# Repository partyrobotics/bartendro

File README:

Programs for the various systems of the Bartendro drink dispensing robot.

Created by Pierre Michael and Robert Kaye
Copyright (c) Party Robotics 2010-2013

All of the source code in this repository is licensed under the GNU Public License 2.0.
The hardware schematic and layouts are licensed using the Creative Commons 
Attribution-ShareAlike 3.0 Unported license.

The source tree is laid out as follows:

hardware -- schematics and layouts for the dispenser and router hardware boards
firmware -- source code (C) for the dispenser and router boards
scripts  -- scripts to make running the bartendro software easier
tsb      -- legacy code from our old skool drink bot prototyp Tequila Sunrise Bot
ui       -- web interface for the bot, written in python.

These various subdirectories may contain more README and COPYING files.

== Downloading updated SD Card images ==

In 2021 the SD card images were updated. They can be downloaded here:

https://github.com/partyrobotics/bartendro/releases/tag/v-2021-05-21

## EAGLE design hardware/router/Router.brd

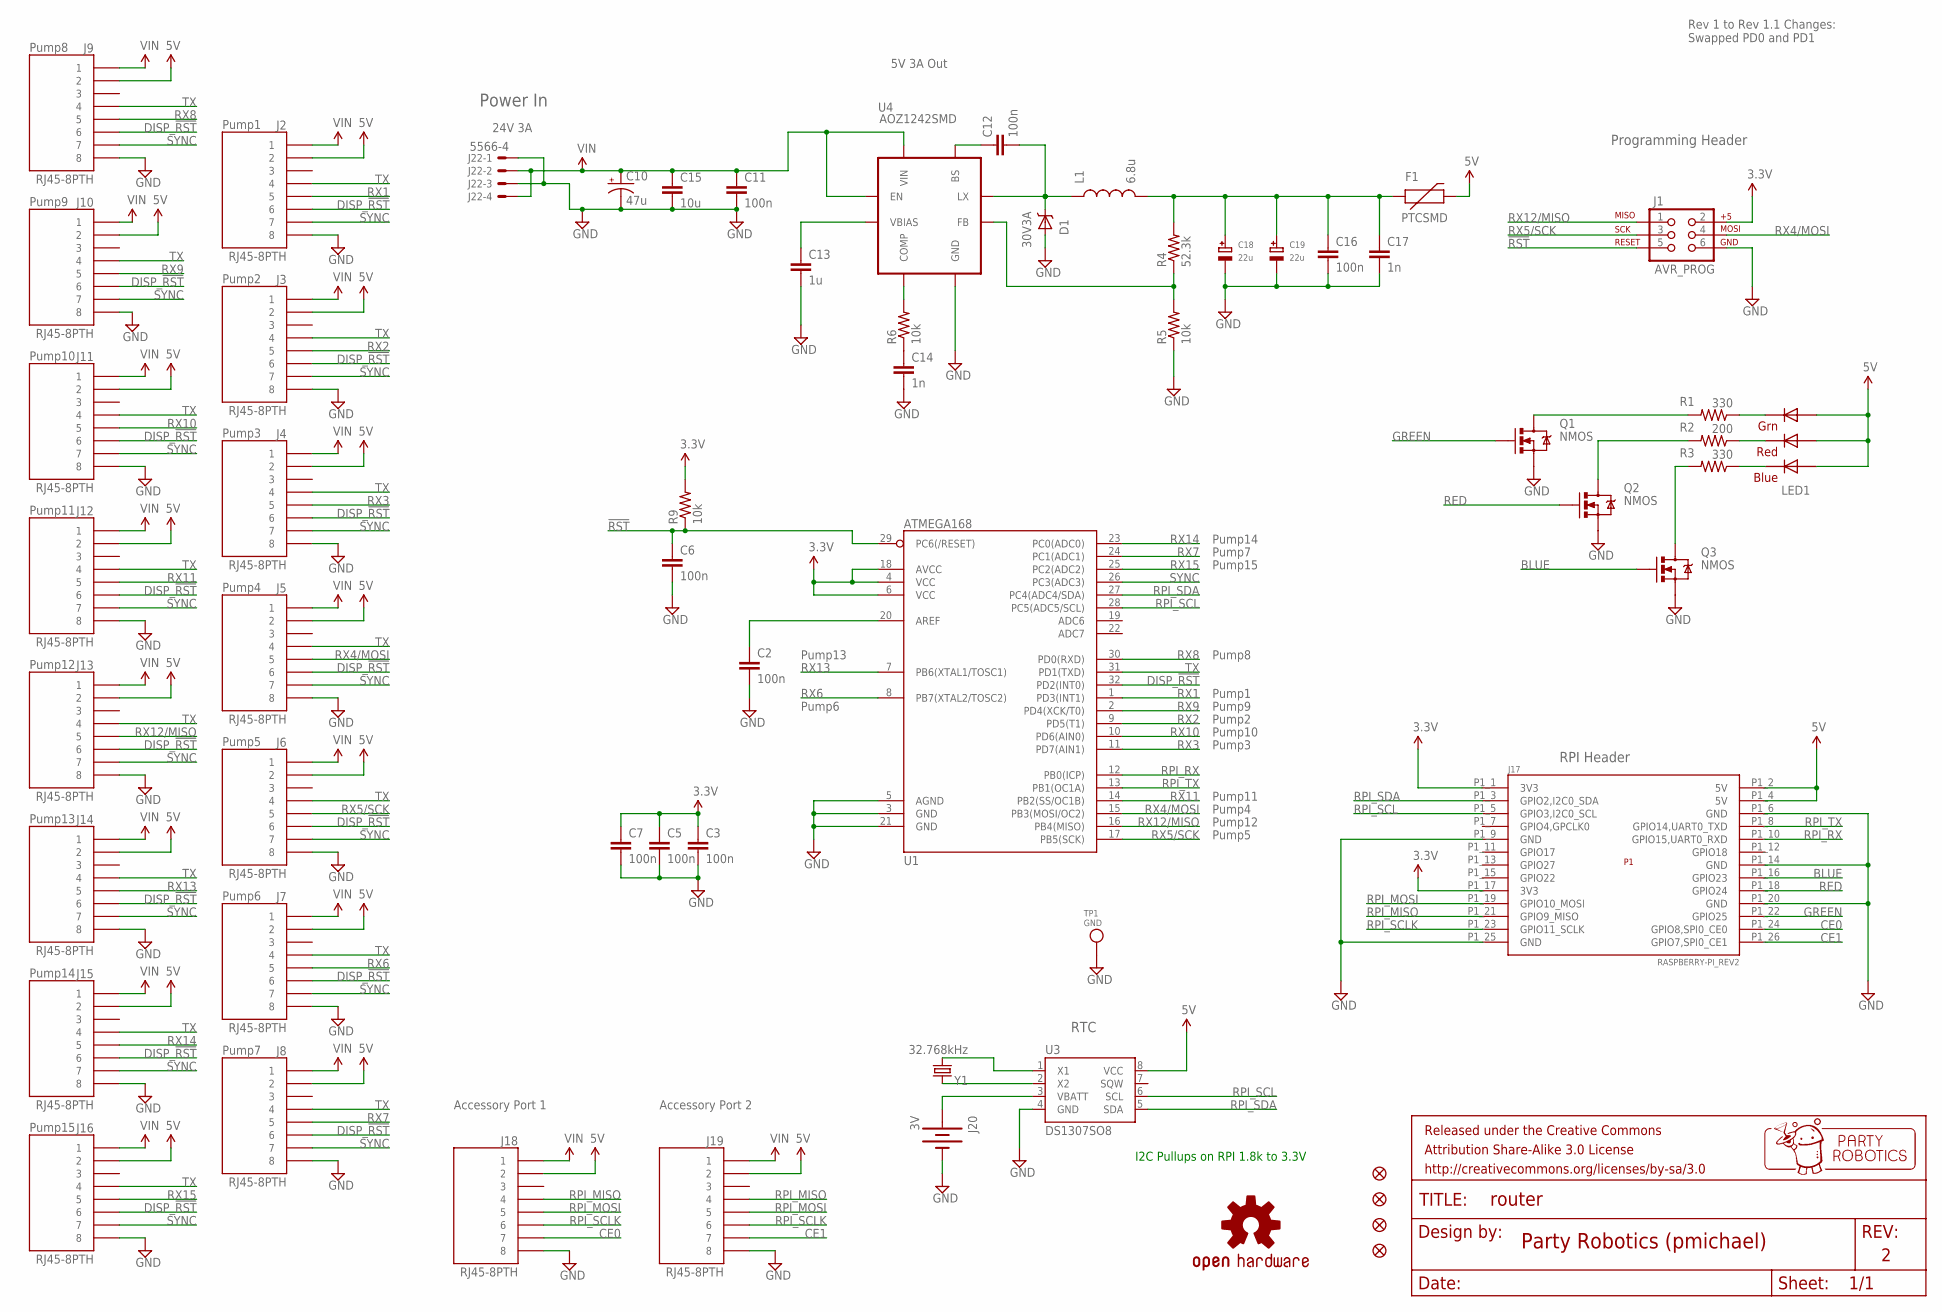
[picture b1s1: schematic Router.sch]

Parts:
C2, C3, C5, C6, C7, C11, C12, C16: 100n; 0603-CAP
C10: 47u; PANASONIC_D
C13: 1u; 0603-CAP
C14, C17: 1n; 0603-CAP
C15: 10u; 1206
C18, C19: 22u; EIA6032-28/C-R
D1: 30V3A; SMA-DIODE
F1: PTCSMD; PTC-1206
FRAME3: FRAME-LETTER; CREATIVE_COMMONS
J1: AVR_PROG; 2X3_LOCK
J2, J3, J4, J5, J6, J7, J8, J10, J11, J12, J13, J14, J15, J16, J18, J19: RJ45-8PTH; RJ45-8; MFG_PN A00-108-220-450
J9: RJ45-8PTH; RJ45-8
J17: RASPBERRY-PI_REV2
J20: 3V; BATTCON_12MM_PTH
J22: 5566-4
JP1, JP2, JP3, JP4: FIDUCIAL1.5X3; FIDUCIAL-1.5X3
L1: 6.8u; IND_8X8X4
LED1: RGBLED5050
Q1, Q2, Q3: NMOS; SOT23-3
R1, R3: 330; 0603-RES
R2: 200; 0603-RES
R4: 52.3k; 0603-RES
R5, R6, R9: 10k; 0603-RES
TP1: GND; TESTPOINT_SMT
U1: ATMEGA168; TQFP32-08
U3: DS1307SO8; SO08
U4: AOZ1242SMD; SO08
U$46: OSHW-LOGOM; OSHW-LOGO-M
Y1: 32.768kHz; TC26HEZ

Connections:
3.3V: C3.1, C5.1, C7.1, J1.2, J17.P1_1 (3V3), J17.P1_17 (3V3), R9.2, U1.4 (VCC), U1.6 (VCC), U1.18 (AVCC)
5V: F1.2, J2.2, J3.2, J4.2, J5.2, J6.2, J7.2, J8.2, J9.2, J10.2, J11.2, J12.2, J13.2, J14.2, J15.2, J16.2, J17.P1_2 (5V), J17.P1_4 (5V), J18.2, J19.2, LED1.1 (BLUE_A), LED1.2 (RED_A), LED1.3 (GREEN_A), U3.8 (VCC)
!RST: C6.1, J1.5, R9.1, U1.29 (PC6(/RESET))
BAT1+: J20.VCC@1 (+), U3.3 (VBATT)
BLUE: J17.P1_16 (GPIO23), Q3.1 (G)
CE0: J17.P1_24 (GPIO8,SPI0_CE0), J18.7
CE1: J17.P1_26 (GPIO7,SPI0_CE1), J19.7
DISP_!RST: J2.6, J3.6, J4.6, J5.6, J6.6, J7.6, J8.6, J9.6, J10.6, J11.6, J12.6, J13.6, J14.6, J15.6, J16.6, U1.32 (PD2(INT0))
GND: C2.2, C3.2, C5.2, C6.2, C7.2, C10.-, C11.2, C13.2, C14.2, C15.2, C16.2, C17.2, C18.-, C19.-, D1.A, J1.6, J2.8, J3.8, J4.8, J5.8, J6.8, J7.8, J8.8, J9.8, J10.8, J11.8, J12.8, J13.8, J14.8, J15.8, J16.8, J17.P1_6 (GND), J17.P1_9 (GND), J17.P1_14 (GND), J17.P1_20 (GND), J17.P1_25 (GND), J18.8, J19.8, J20.GND (-), J22.1, J22.3, Q1.2 (S), Q2.2 (S), Q3.2 (S), R5.1, TP1.P$1, U1.3 (GND), U1.5 (AGND), U1.21 (GND), U3.4 (GND), U4.3 (GND)
GREEN: J17.P1_22 (GPIO25), Q1.1 (G)
unnamed: U3.2 (X2), Y1.1
unnamed: R4.1, R5.2, U4.4 (FB)
unnamed: R6.2, U4.5 (COMP)
unnamed: C2.1, U1.20 (AREF)
unnamed: C16.1, C17.1, C18.+, C19.+, F1.1, L1.P$2 (2), R4.2
unnamed: U3.1 (X1), Y1.2
unnamed: C12.1, U4.2 (BS)
unnamed: C13.1, U4.8 (VBIAS)
unnamed: LED1.4 (GREEN_C), R1.1
unnamed: Q1.3 (D), R1.2
unnamed: Q2.3 (D), R2.2
unnamed: LED1.5 (RED_C), R2.1
unnamed: LED1.6 (BLUE_C), R3.1
unnamed: Q3.3 (D), R3.2
unnamed: C14.1, R6.1
unnamed: C12.2, D1.C, L1.P$1 (1), U4.1 (LX)
RED: J17.P1_18 (GPIO24), Q2.1 (G)
RPI_MISO: J17.P1_21 (GPIO9_MISO), J18.4, J19.4
RPI_MOSI: J17.P1_19 (GPIO10_MOSI), J18.5, J19.5
RPI_RX: J17.P1_10 (GPIO15,UART0_RXD), U1.12 (PB0(ICP))
RPI_SCL: J17.P1_5 (GPIO3,I2C0_SCL), U1.28 (PC5(ADC5/SCL)), U3.6 (SCL)
RPI_SCLK: J17.P1_23 (GPIO11_SCLK), J18.6, J19.6
RPI_SDA: J17.P1_3 (GPIO2,I2C0_SDA), U1.27 (PC4(ADC4/SDA)), U3.5 (SDA)
RPI_TX: J17.P1_8 (GPIO14,UART0_TXD), U1.13 (PB1(OC1A))
RX1: J2.5, U1.1 (PD3(INT1))
RX2: J3.5, U1.9 (PD5(T1))
RX3: J4.5, U1.11 (PD7(AIN1))
RX4/MOSI: J1.4, J5.5, U1.15 (PB3(MOSI/OC2))
RX5/SCK: J1.3, J6.5, U1.17 (PB5(SCK))
RX6: J7.5, U1.8 (PB7(XTAL2/TOSC2))
RX7: J8.5, U1.24 (PC1(ADC1))
RX8: J9.5, U1.30 (PD0(RXD))
RX9: J10.5, U1.2 (PD4(XCK/T0))
RX10: J11.5, U1.10 (PD6(AIN0))
RX11: J12.5, U1.14 (PB2(SS/OC1B))
RX12/MISO: J1.1, J13.5, U1.16 (PB4(MISO))
RX13: J14.5, U1.7 (PB6(XTAL1/TOSC1))
RX14: J15.5, U1.23 (PC0(ADC0))
RX15: J16.5, U1.25 (PC2(ADC2))
SYNC: J2.7, J3.7, J4.7, J5.7, J6.7, J7.7, J8.7, J9.7, J10.7, J11.7, J12.7, J13.7, J14.7, J15.7, J16.7, U1.26 (PC3(ADC3))
TX: J2.4, J3.4, J4.4, J5.4, J6.4, J7.4, J8.4, J9.4, J10.4, J11.4, J12.4, J13.4, J14.4, J15.4, J16.4, U1.31 (PD1(TXD))
VIN: C10.+, C11.1, C15.1, J2.1, J3.1, J4.1, J5.1, J6.1, J7.1, J8.1, J9.1, J10.1, J11.1, J12.1, J13.1, J14.1, J15.1, J16.1, J18.1, J19.1, J22.2, J22.4, U4.6 (EN), U4.7 (VIN)

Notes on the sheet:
Programming Header
RTC
Accessory Port 1
I2C Pullups on RPI 1.8k to 3.3V
Accessory Port 2
Pump1
Pump2
Pump9
Pump8
Pump10
Pump11
Pump3
Pump4
Pump12
Pump5
Pump13
Pump6
Pump14
Pump7
Pump15
Rev 1 to Rev 1.1 Changes: Swapped PD0 and PD1
Party Robotics (pmichael)
5V 3A Out
Power In
24V 3A
RPI Header

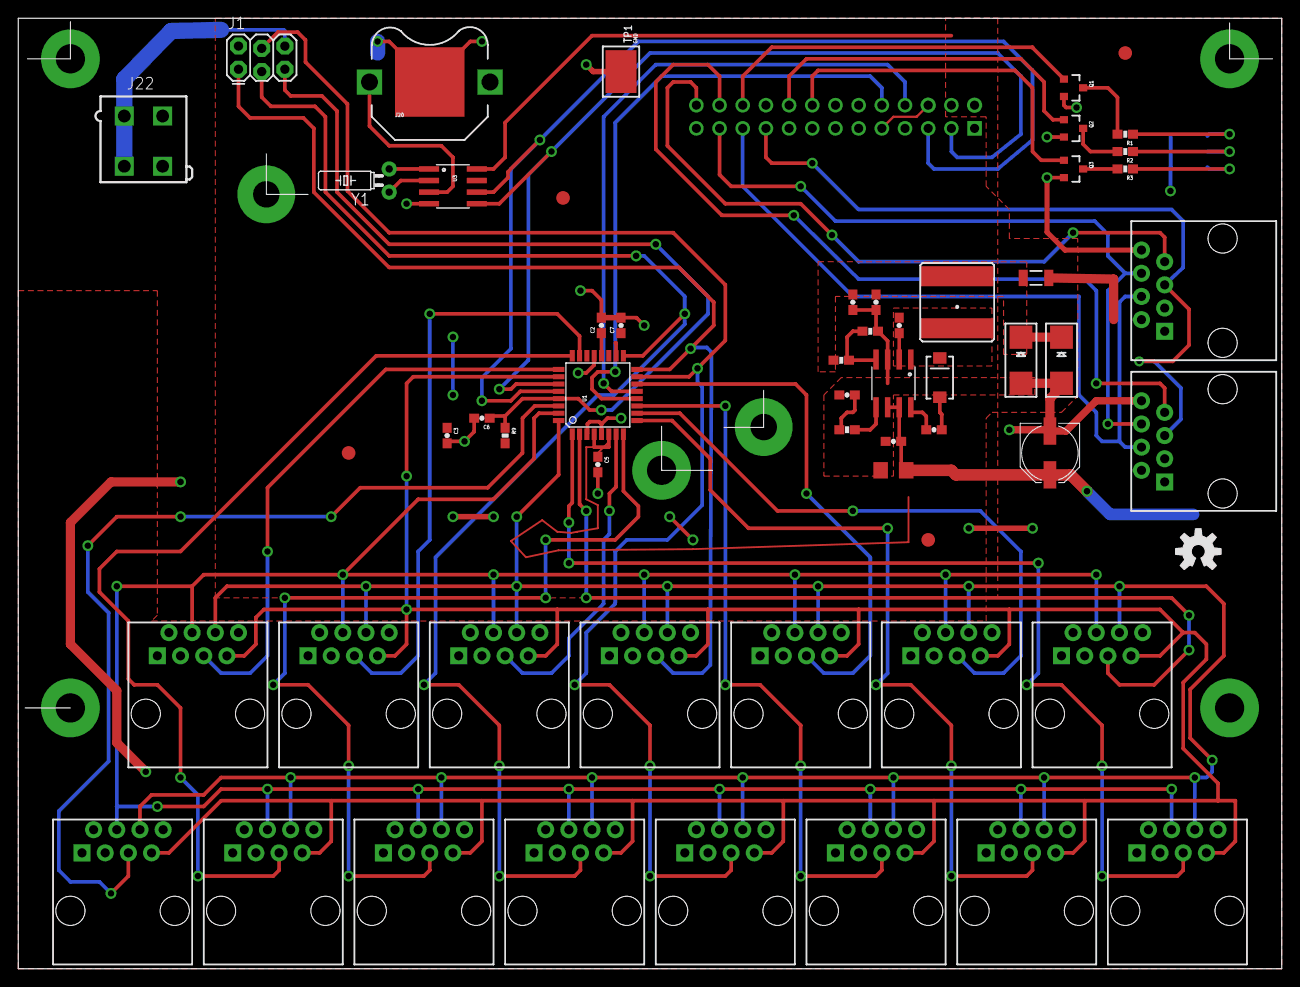
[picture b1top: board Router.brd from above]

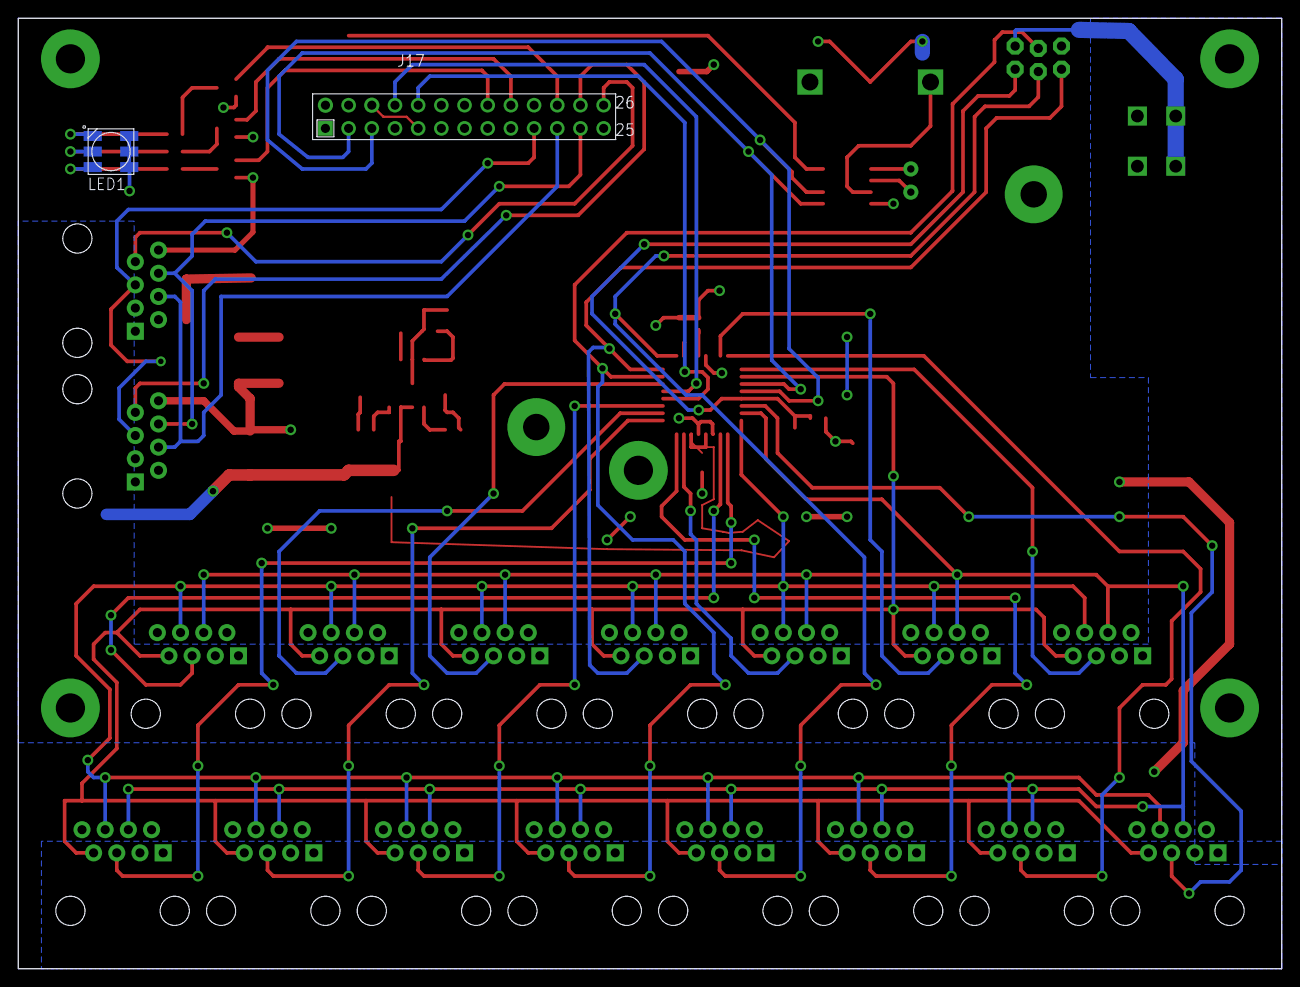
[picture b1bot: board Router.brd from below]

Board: 2 copper layers, 138.4 x 104.1 mm, 61 parts (2 on the bottom side), 52 nets.

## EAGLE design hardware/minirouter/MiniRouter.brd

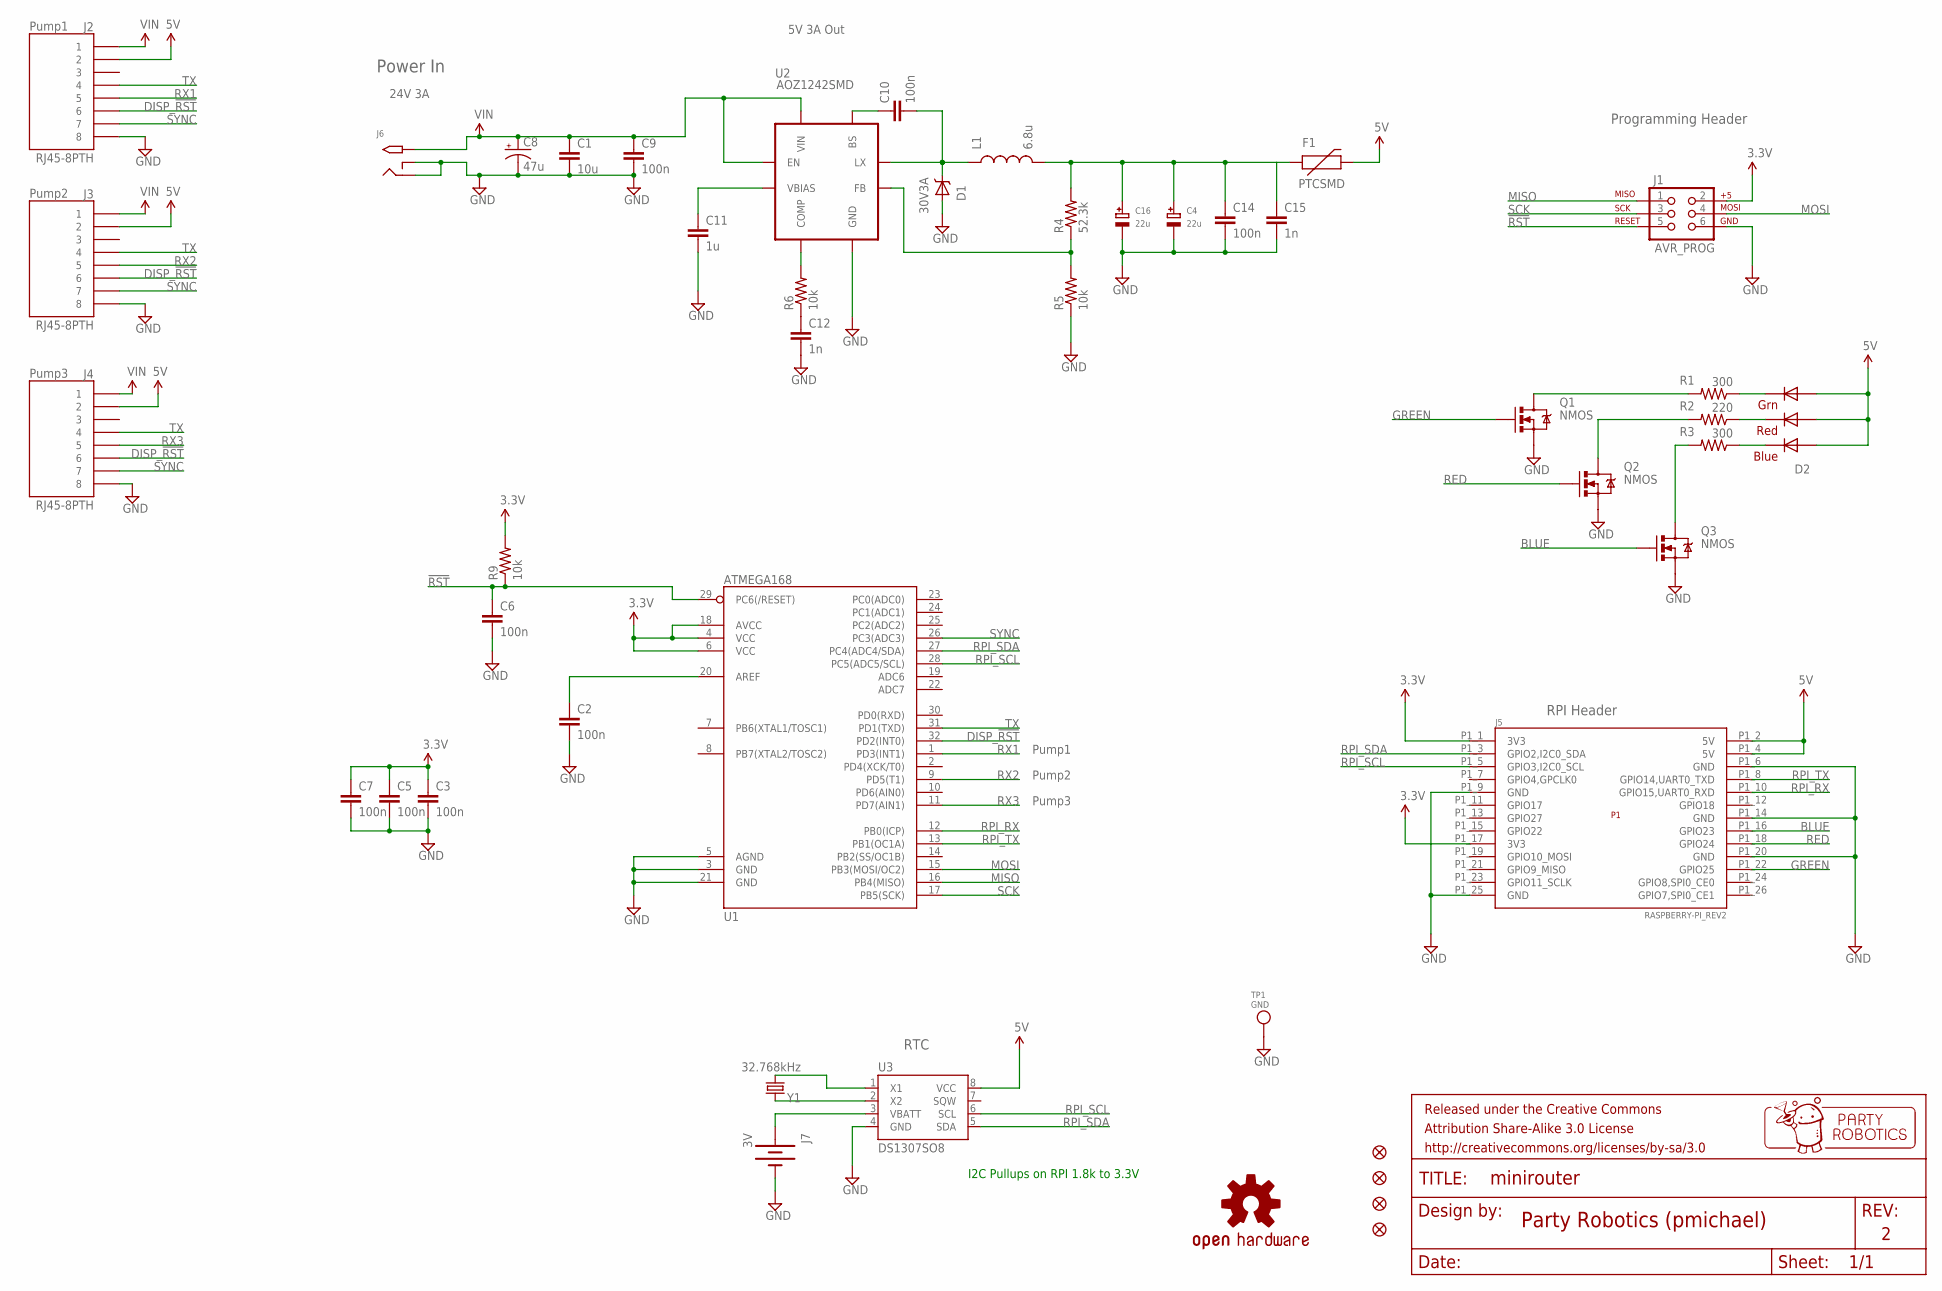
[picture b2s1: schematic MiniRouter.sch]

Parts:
C1: 10u; 1206
C2, C3, C5, C6, C7, C9, C10, C14: 100n; 0603-CAP
C4, C16: 22u; EIA6032-28/C-R
C8: 47u; PANASONIC_D
C11: 1u; 0603-CAP
C12, C15: 1n; 0603-CAP
D1: 30V3A; SMA-DIODE
D2: RGBLED5050
F1: PTCSMD; PTC-1206
FRAME3: FRAME-LETTER; CREATIVE_COMMONS
J1: AVR_PROG; 2X3_LOCK
J2, J3, J4: RJ45-8PTH; RJ45-8
J5: RASPBERRY-PI_REV2
J6: 2.1MMJACKTHM; PJ-102A
J7: 3V; BATTCON_12MM_PTH
JP1, JP2, JP3, JP4: FIDUCIAL1.5X3; FIDUCIAL-1.5X3
L1: 6.8u; IND_8X8X4
Q1, Q2, Q3: NMOS; SOT23-3
R1, R3: 300; 0603-RES
R2: 220; 0603-RES
R4: 52.3k; 0603-RES
R5, R6, R9: 10k; 0603-RES
TP1: GND; TESTPOINT_SMT
U1: ATMEGA168; TQFP32-08
U2: AOZ1242SMD; SO08
U3: DS1307SO8; SO08
U$46: OSHW-LOGOM; OSHW-LOGO-M
Y1: 32.768kHz; TC26HEZ

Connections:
3.3V: C3.1, C5.1, C7.1, J1.2, J5.P1_1 (3V3), J5.P1_17 (3V3), R9.2, U1.4 (VCC), U1.6 (VCC), U1.18 (AVCC)
5V: D2.1 (BLUE_A), D2.2 (RED_A), D2.3 (GREEN_A), F1.2, J2.2, J3.2, J4.2, J5.P1_2 (5V), J5.P1_4 (5V), U3.8 (VCC)
!RST: C6.1, J1.5, R9.1, U1.29 (PC6(/RESET))
BAT1+: J7.VCC@1 (+), U3.3 (VBATT)
BLUE: J5.P1_16 (GPIO23), Q3.1 (G)
DISP_!RST: J2.6, J3.6, J4.6, U1.32 (PD2(INT0))
GND: C1.2, C2.2, C3.2, C4.-, C5.2, C6.2, C7.2, C8.-, C9.2, C11.2, C12.2, C14.2, C15.2, C16.-, D1.A, J1.6, J2.8, J3.8, J4.8, J5.P1_6 (GND), J5.P1_9 (GND), J5.P1_14 (GND), J5.P1_20 (GND), J5.P1_25 (GND), J6.RING, J6.RING_SW, J7.GND (-), Q1.2 (S), Q2.2 (S), Q3.2 (S), R5.1, TP1.P$1, U1.3 (GND), U1.5 (AGND), U1.21 (GND), U2.3 (GND), U3.4 (GND)
GREEN: J5.P1_22 (GPIO25), Q1.1 (G)
MISO: J1.1, U1.16 (PB4(MISO))
MOSI: J1.4, U1.15 (PB3(MOSI/OC2))
unnamed: U3.2 (X2), Y1.1
unnamed: R4.1, R5.2, U2.4 (FB)
unnamed: R6.2, U2.5 (COMP)
unnamed: C2.1, U1.20 (AREF)
unnamed: C4.+, C14.1, C15.1, C16.+, F1.1, L1.P$2 (2), R4.2
unnamed: U3.1 (X1), Y1.2
unnamed: C10.1, U2.2 (BS)
unnamed: C11.1, U2.8 (VBIAS)
unnamed: D2.4 (GREEN_C), R1.1
unnamed: Q1.3 (D), R1.2
unnamed: Q2.3 (D), R2.2
unnamed: D2.5 (RED_C), R2.1
unnamed: D2.6 (BLUE_C), R3.1
unnamed: Q3.3 (D), R3.2
unnamed: C12.1, R6.1
unnamed: C10.2, D1.C, L1.P$1 (1), U2.1 (LX)
RED: J5.P1_18 (GPIO24), Q2.1 (G)
RPI_RX: J5.P1_10 (GPIO15,UART0_RXD), U1.12 (PB0(ICP))
RPI_SCL: J5.P1_5 (GPIO3,I2C0_SCL), U1.28 (PC5(ADC5/SCL)), U3.6 (SCL)
RPI_SDA: J5.P1_3 (GPIO2,I2C0_SDA), U1.27 (PC4(ADC4/SDA)), U3.5 (SDA)
RPI_TX: J5.P1_8 (GPIO14,UART0_TXD), U1.13 (PB1(OC1A))
RX1: J2.5, U1.1 (PD3(INT1))
RX2: J3.5, U1.9 (PD5(T1))
RX3: J4.5, U1.11 (PD7(AIN1))
SCK: J1.3, U1.17 (PB5(SCK))
SYNC: J2.7, J3.7, J4.7, U1.26 (PC3(ADC3))
TX: J2.4, J3.4, J4.4, U1.31 (PD1(TXD))
VIN: C1.1, C8.+, C9.1, J2.1, J3.1, J4.1, J6.TIP, U2.6 (EN), U2.7 (VIN)

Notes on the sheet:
Programming Header
RPI Header
RTC
5V 3A Out
Power In
I2C Pullups on RPI 1.8k to 3.3V
Pump2
Pump3
Pump1
Party Robotics (pmichael)
24V 3A

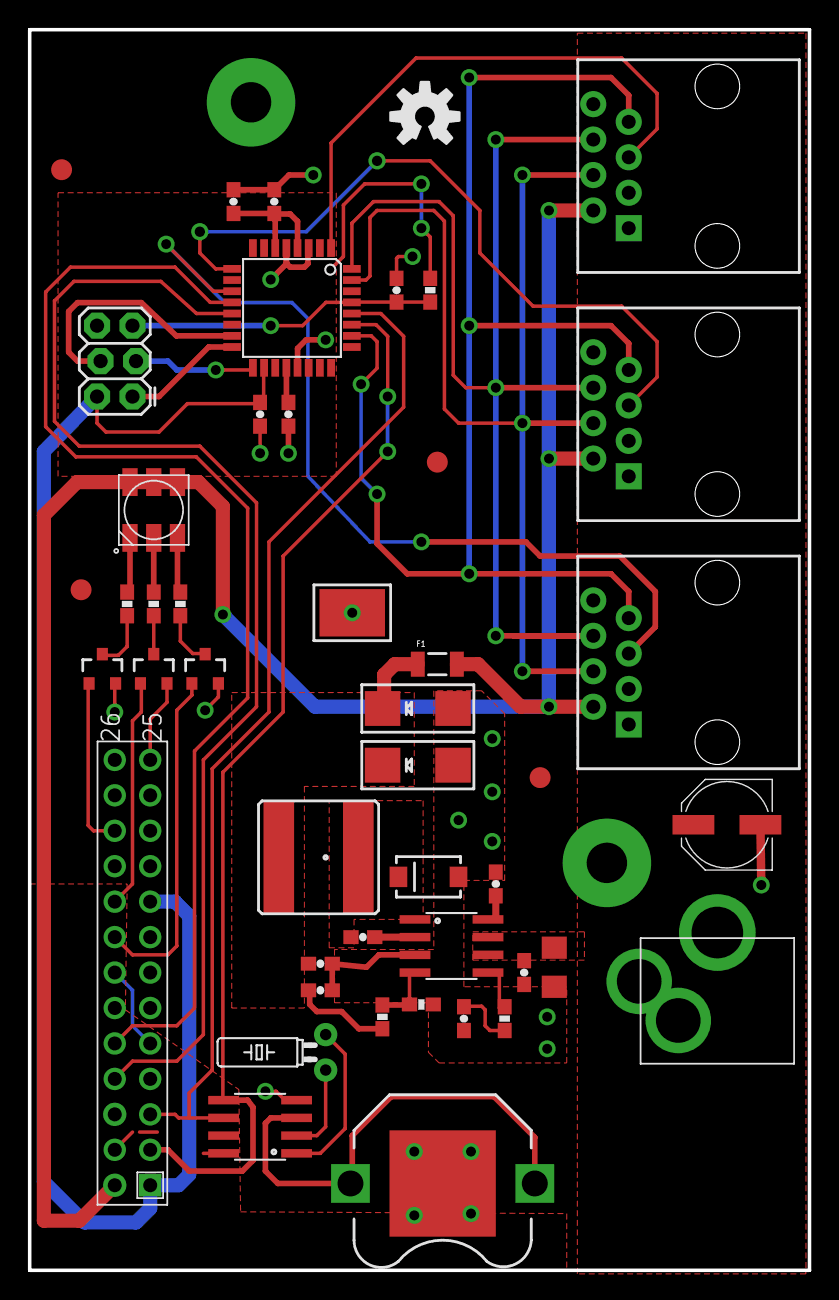
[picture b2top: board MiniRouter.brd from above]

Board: 2 copper layers, 55.9 x 88.9 mm, 47 parts (0 on the bottom side), 38 nets.

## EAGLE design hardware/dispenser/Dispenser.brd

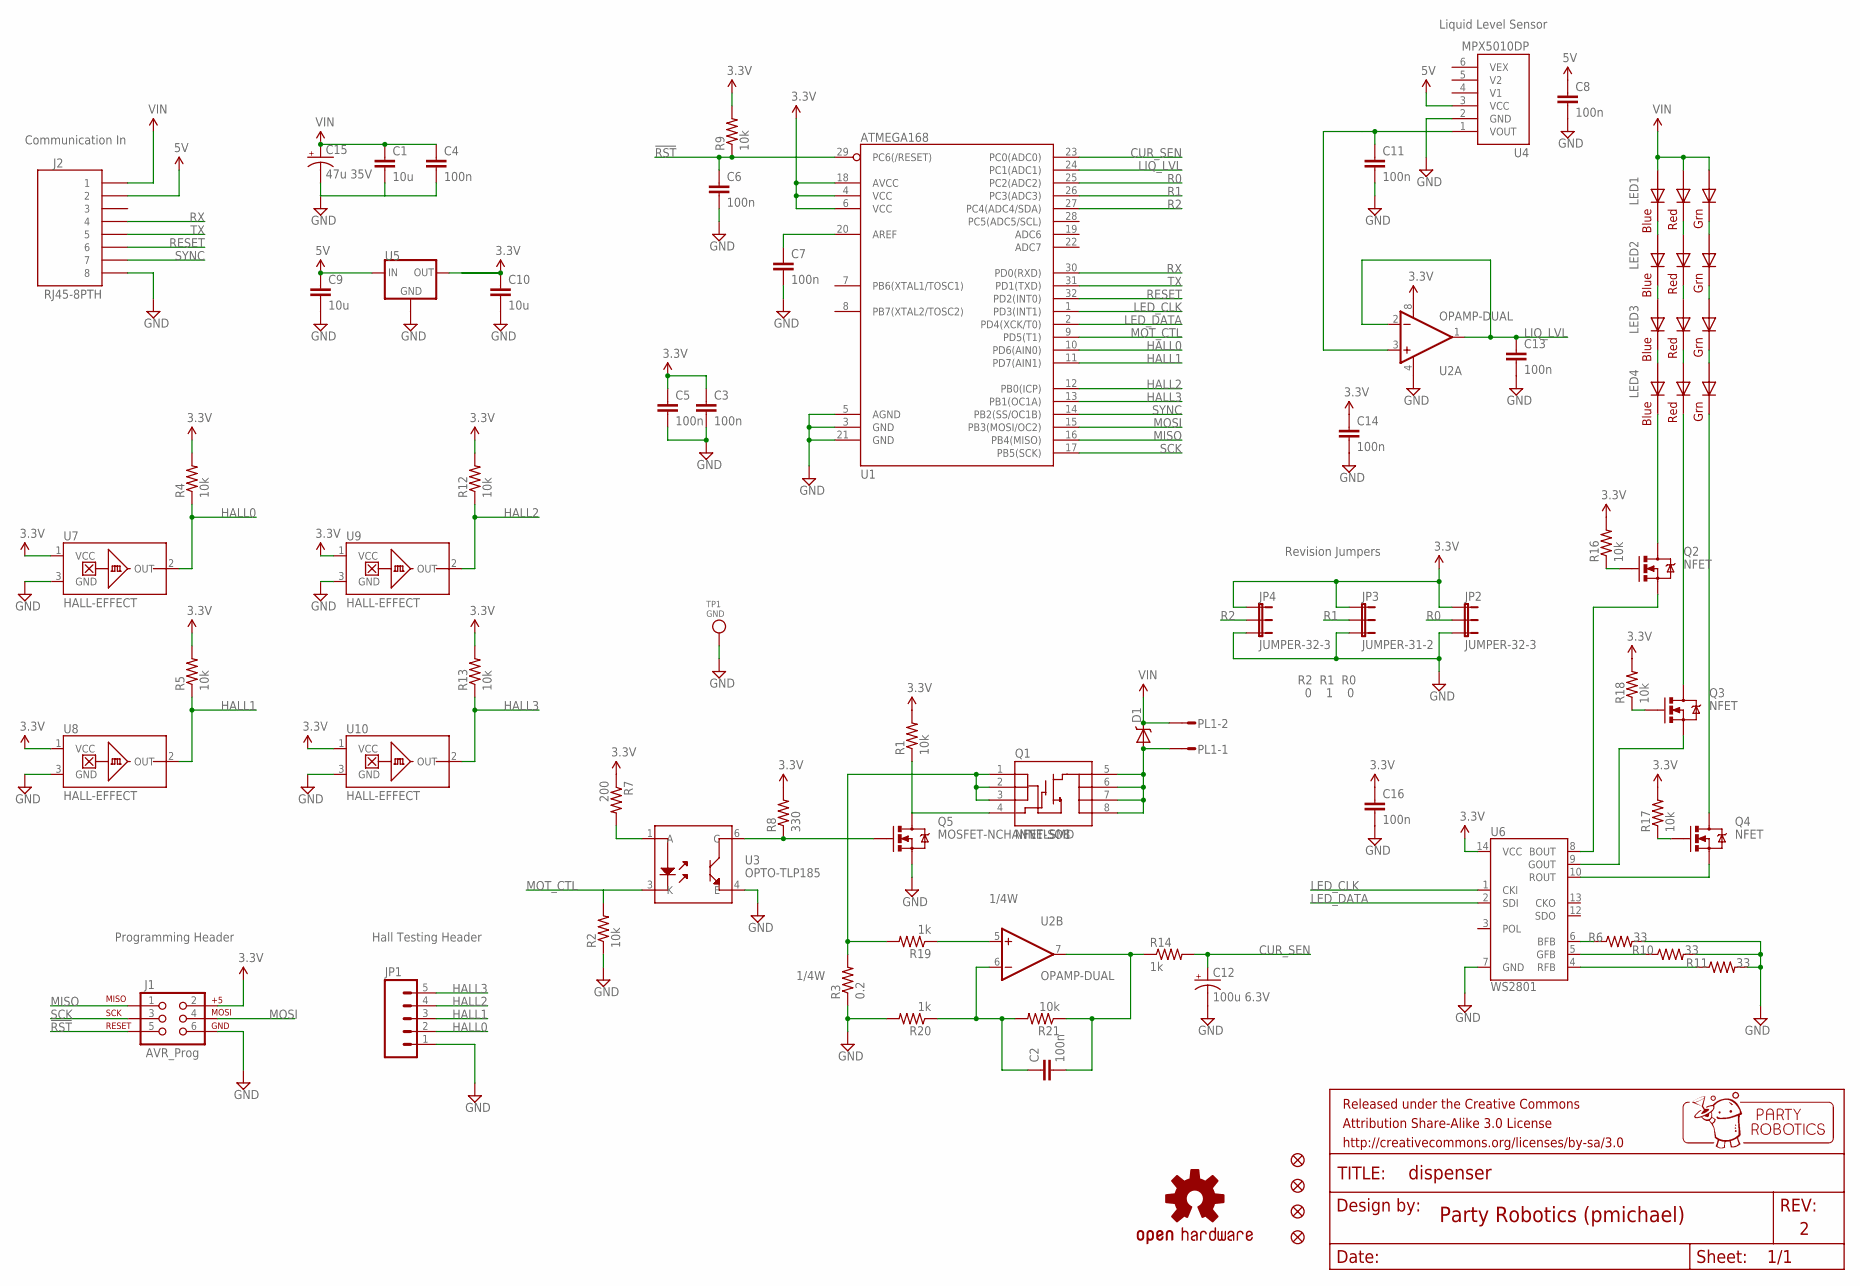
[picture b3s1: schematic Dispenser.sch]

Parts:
C1, C9, C10: 10u; 0603-CAP
C2, C3, C4, C5, C6, C7, C8, C11, C13, C14, C16: 100n; 0603-CAP
C12: 100u 6.3V; PANASONIC_D
C15: 47u 35V; PANASONIC_D
D1: B330A; SMA-DIODE
FRAME3: FRAME-LETTER; CREATIVE_COMMONS
J1: AVR_Prog; 2X3_LOCK
J2: RJ45-8PTH; RJ45-8
JP1: M051.27MM; 1X05-1.27MM
JP2, JP4: JUMPER-32-3; SJ_3_PASTE2&3
JP3: JUMPER-31-2; SJ_3_PASTE1&2
JP5, JP6, JP7, JP8: FIDUCIAL1X2; FIDUCIAL-1X2
LED1, LED2, LED3, LED4: RGBLED5050
PL1: DF3-02P; DF3P-02
Q1: NFET-SO8; SO08
Q2, Q3, Q4: NFET; SOT23-3
Q5: MOSFET-NCHANNELSMD; SOT23-3
R1, R2, R4, R5, R9, R12, R13, R16, R17, R18, R21: 10k; 0603-RES
R3: 0.2; 0805
R6, R10, R11: 33; 0603-RES
R7: 200; 0603-RES
R8: 330; 0603-RES
R14, R19, R20: 1k; 0603-RES
TP1: GND; TESTPOINT_SMT
U1: ATMEGA168; TQFP32-08
U2: OPAMP-DUAL; SO08
U3: OPTO-TLP185; SO6
U4: MPX5010DP
U5: VREG-5V-LDO-AP1117SOT89-3L; SOT89-3L
U6: WS2801; SOP-14
U7, U8, U9, U10: HALL-EFFECT; SOT23-3
U$1: OSHW-LOGOM; OSHW-LOGO-M

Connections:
1/4W: Q1.1 (S), Q1.2 (S), Q1.3 (S), R3.2, R19.2
3.3V: C3.1, C5.1, C8.1, C10.1, C14.1, C16.1, J1.2, JP2.1, JP3.1, JP4.1, R1.2, R4.2, R5.2, R7.1, R8.2, R9.2, R12.2, R13.2, R16.2, R17.2, R18.2, U1.4 (VCC), U1.6 (VCC), U1.18 (AVCC), U2.8 (V+), U5.2 (OUT), U5.2.1 (OUT), U6.14 (VCC), U7.1 (VCC), U8.1 (VCC), U9.1 (VCC), U10.1 (VCC)
5V: C9.1, J2.2, U4.3 (VCC), U5.3 (IN)
!RST: C6.1, J1.5, R9.1, U1.29 (PC6(/RESET))
BLUE: Q2.2 (S), U6.8 (BOUT)
CUR_SEN: C12.+, R14.2, U1.23 (PC0(ADC0))
GND: C1.2, C3.2, C4.2, C5.2, C6.2, C7.2, C8.2, C9.2, C10.2, C11.2, C12.-, C13.2, C14.2, C15.-, C16.2, J1.6, J2.8, JP1.1, JP2.3, JP3.3, JP4.3, Q5.2 (S), R2.1, R3.1, R6.2, R10.2, R11.2, R20.2, TP1.P$1, U1.3 (GND), U1.5 (AGND), U1.21 (GND), U2.4 (V-), U3.4 (E), U4.2 (GND), U5.1 (GND), U6.7 (GND), U7.3 (GND), U8.3 (GND), U9.3 (GND), U10.3 (GND)
GREEN: Q3.2 (S), U6.9 (GOUT)
HALL0: JP1.2, R4.1, U1.10 (PD6(AIN0)), U7.2 (OUT)
HALL1: JP1.3, R5.1, U1.11 (PD7(AIN1)), U8.2 (OUT)
HALL2: JP1.4, R12.1, U1.12 (PB0(ICP)), U9.2 (OUT)
HALL3: JP1.5, R13.1, U1.13 (PB1(OC1A)), U10.2 (OUT)
LED_CLK: U1.1 (PD3(INT1)), U6.1 (CKI)
LED_DATA: U1.2 (PD4(XCK/T0)), U6.2 (SDI)
LIQ_LVL: C13.1, U1.24 (PC1(ADC1)), U2.1 (OUT), U2.2 (-IN)
MISO: J1.1, U1.16 (PB4(MISO))
MOSI: J1.4, U1.15 (PB3(MOSI/OC2))
MOT_B: D1.A, PL1.1, Q1.5 (D), Q1.6 (D), Q1.7 (D), Q1.8 (D)
MOT_CTL: R2.2, U1.9 (PD5(T1)), U3.3 (K)
MOT_CUR: C2.2, R14.1, R21.1, U2.7 (OUT)
unnamed: C7.1, U1.20 (AREF)
unnamed: Q3.1 (G), R18.1
unnamed: Q4.1 (G), R17.1
unnamed: Q2.1 (G), R16.1
unnamed: R6.1, U6.6 (BFB)
unnamed: R10.1, U6.5 (GFB)
unnamed: R11.1, U6.4 (RFB)
unnamed: Q1.4 (G), Q5.3 (D), R1.1
unnamed: C2.1, R20.1, R21.2, U2.6 (-IN)
unnamed: R19.1, U2.5 (+IN)
unnamed: LED4.6 (BLUE_C), Q2.3 (D)
unnamed: LED4.5 (RED_C), Q3.3 (D)
unnamed: LED4.4 (GREEN_C), Q4.3 (D)
unnamed: R7.2, U3.1 (A)
unnamed: Q4.2 (S), U6.10 (ROUT)
unnamed: C11.1, U2.3 (+IN), U4.1 (VOUT)
unnamed: LED3.6 (BLUE_C), LED4.1 (BLUE_A)
unnamed: Q5.1 (G), R8.1, U3.6 (C)
unnamed: LED3.5 (RED_C), LED4.2 (RED_A)
unnamed: LED3.4 (GREEN_C), LED4.3 (GREEN_A)
unnamed: LED2.4 (GREEN_C), LED3.3 (GREEN_A)
unnamed: LED2.5 (RED_C), LED3.2 (RED_A)
unnamed: LED2.6 (BLUE_C), LED3.1 (BLUE_A)
unnamed: LED1.4 (GREEN_C), LED2.3 (GREEN_A)
unnamed: LED1.5 (RED_C), LED2.2 (RED_A)
unnamed: LED1.6 (BLUE_C), LED2.1 (BLUE_A)
R0: JP2.2, U1.25 (PC2(ADC2))
R1: JP3.2, U1.26 (PC3(ADC3))
R2: JP4.2, U1.27 (PC4(ADC4/SDA))
RESET: J2.6, U1.32 (PD2(INT0))
RX: J2.4, U1.30 (PD0(RXD))
SCK: J1.3, U1.17 (PB5(SCK))
SYNC: J2.7, U1.14 (PB2(SS/OC1B))
TX: J2.5, U1.31 (PD1(TXD))
VIN: C1.1, C4.1, C15.+, D1.C, J2.1, LED1.1 (BLUE_A), LED1.2 (RED_A), LED1.3 (GREEN_A), PL1.2

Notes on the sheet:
Programming Header
Liquid Level Sensor
Party Robotics (pmichael)
Hall Testing Header
Communication In
Revision Jumpers
R2 R1 R0
0 1 0

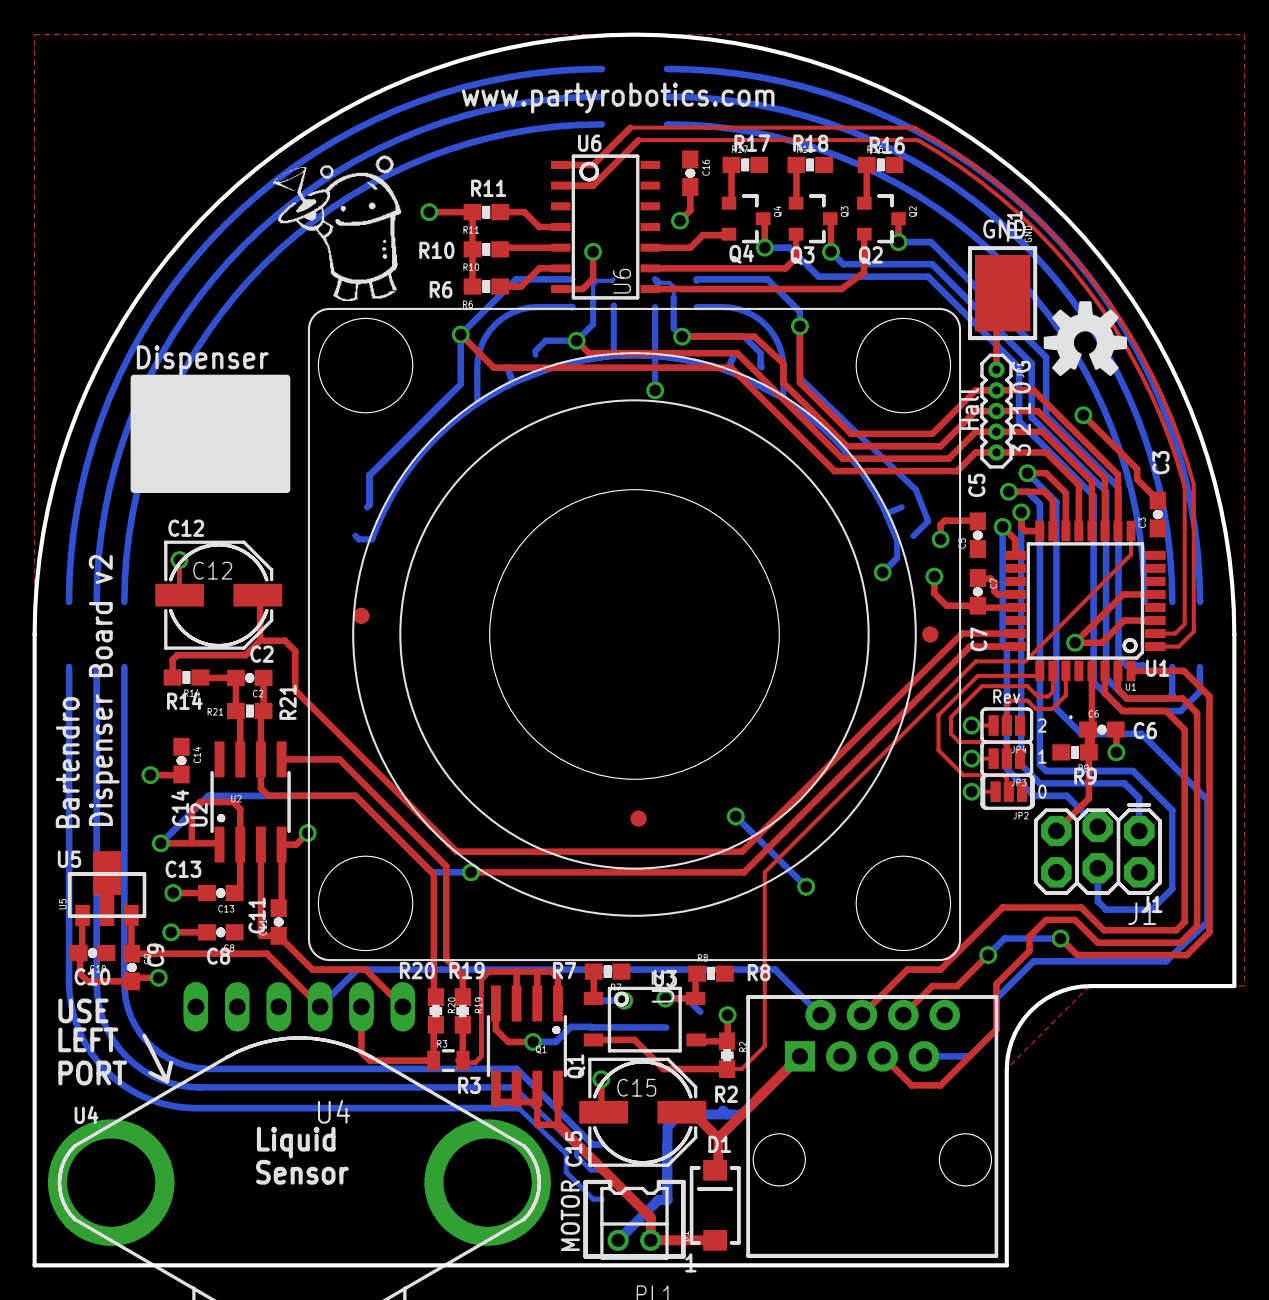
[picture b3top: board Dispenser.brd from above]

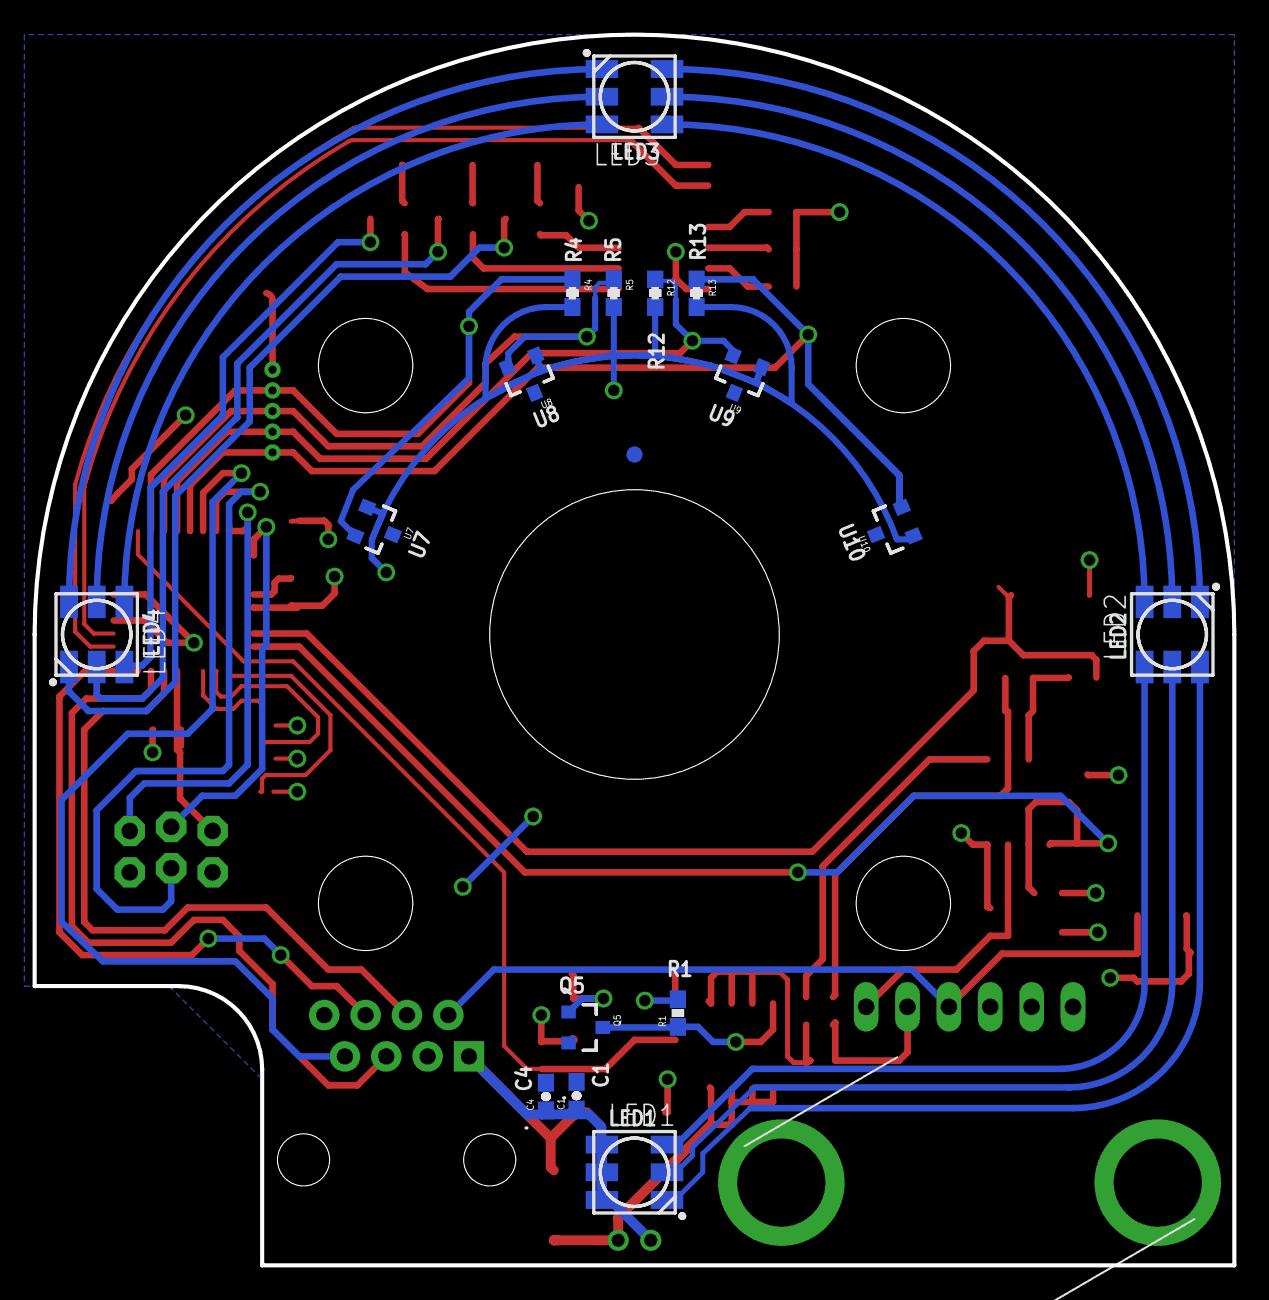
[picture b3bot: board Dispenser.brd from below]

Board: 2 copper layers, 73.7 x 75.6 mm, 70 parts (17 on the bottom side), 55 nets.

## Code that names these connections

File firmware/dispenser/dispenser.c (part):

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void set_led_pattern(uint8_t pattern);

/*
   0  - PD0 - RX
   1  - PD1 - TX
   2  - PD2 - RESET
   3  - PD3 - LED clock
   4  - PD4 - LED data
   5  - PD5 - motor control B (OC0B)
   6  - PD6 - motor control A (OC0A)
   7  - PD7 - Hall 0 (pcint 23)
   8  - PB0 - Hall 1 (pcint 0)
   9  - PB1 - Hall 2 (pcint 1) 
  10  - PB2 - Hall 3 (pcint 2)
  14  - PB6 - /RTRY for motor driver
  15  - PB7 - BUTTON (pcint7)
  A0  - PC0 - Current Sense (since v3 a digital function) (pcint 8)
  A1  - PC1 - liquid level
  A2  - PC2 - REV0
  A3  - PC3 - REV1
  A4  - PC4 - REV2
  A5  - PC5 - SYNC (pcint13)

*/
void setup(void)
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    serial_init();

    // Set up LEDs & motor control outputs
    DDRD |= (1<<PD3)|(1<<PD4)|(1<<PD5)|(1<<PD6);
    DDRB |= (1<<PB6);

    // pull ups for hall sensors & for current sense
    sbi(PORTD, 7);
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
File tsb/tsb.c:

#include <avr/io.h>
#include <stdint.h>
#include <stdlib.h>
#include <string.h>
#include <avr/interrupt.h>
#include <avr/pgmspace.h>
#include <util/delay.h>

#include "debug.h"

// Bit manipulation macros
#define sbi(a, b) ((a) |= 1 << (b))       //sets bit B in variable A
#define cbi(a, b) ((a) &= ~(1 << (b)))    //clears bit B in variable A
#define tbi(a, b) ((a) ^= 1 << (b))       //toggles bit B in variable A

#define MAX_MOTORS 3
typedef struct
{
    int8_t   motor;
    uint16_t duration;
} motor_cmd;

int compare(void *a, void *b)
{
    return ((motor_cmd *)a)->duration > ((motor_cmd *)b)->duration;
}

void run(uint8_t count, motor_cmd *cmds)
{
    uint8_t  i;
    uint16_t t = 0, duration;

    qsort(cmds, count, sizeof(motor_cmd), compare);

    for(i = 0; i < count; i++)
        dprintf("%05u: motor %d on, %u ms\n", t, cmds[i].motor, cmds[i].duration);
    
    // turn motors on
    for(i = 0; i < count; i++)
    {
        if (cmds[i].motor == 0)
            sbi(PORTB, 0);
        if (cmds[i].motor == 1)
            sbi(PORTB, 1);
        if (cmds[i].motor == 2)
            sbi(PORTB, 2);
    }
    for(i = 0; i < count; i++)
    {
        duration = cmds[i].duration - t;
        dprintf("delay: %d\n", duration);
        while(duration > 0)
        {
            uint8_t d = duration > 10 ? 10 : duration;
            _delay_ms(d);
            duration -= d;
            t += d;
        }
        if (cmds[i].motor == 0)
            cbi(PORTB, 0);
        if (cmds[i].motor == 1)
            cbi(PORTB, 1);
        if (cmds[i].motor == 2)
            cbi(PORTB, 2);
    }
}

static motor_cmd drinks[3][3] =
{
//    { // Test
//        { 0, 400 },
//        { 1, 2000 },
//        { 2, 1333 }
//    },
    { // Normal
        { 0, 3560 },
        { 1, 21360 },
        { 2, 10680 }
    },
    { // Strong
        { 0, 3830 },
        { 1, 19150 },
        { 2, 12770 }
    }
};

int main(void)
{
    uint8_t   i;

    serial_init();

    // Set PWM pins as outputs
    DDRB |= (1<<PB0)|(1<<PB1)|(1<<PB2);
    DDRB |= (1<<PB4)|(1<<PB3);

    /*
    for(i = 0; i < 3; i++)
    {
        sbi(PORTB, 0);
        sbi(PORTB, 1);
        sbi(PORTB, 2);
        _delay_ms(50);

        cbi(PORTB, 0);
        cbi(PORTB, 1);
        cbi(PORTB, 2);
        _delay_ms(50);
    }
    */

    dprintf("\nTequila Sunrise bot. What shall be your bidding?\n\n");
    for(;;)
    {
        if (!(PIND & (1<<PIND7)))
        {
            sbi(PORTB, 3);
            dprintf("making normal drink\n");
            run(3, drinks[0]);
            dprintf("drink complete. bottoms up!\n");
            cbi(PORTB, 3);
        }
        if (!(PIND & (1<<PIND6)))
        {
            sbi(PORTB, 4);
            dprintf("making strong drink\n");
            run(3, drinks[1]);
            dprintf("drink complete. bottoms up!\n");
            cbi(PORTB, 4);
        }
    }
	return 0;
}

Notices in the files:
hardware/dispenser/Dispenser.brd:
Released under the Creative Commons Attribution Share-Alike 3.0 License
http://creativecommons.org/licenses/by-sa/3.0
hardware/minirouter/MiniRouter.brd:
(c) 2013
parts and their libraries:
SparkFun-Resistors: Licensing: CC v3.0 Share-Alike You are welcome to use this library for commercial purposes.
microbuilder: This work is placed in the public domain, and may be freely used for commercial and non-commercial work with the following conditions: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
